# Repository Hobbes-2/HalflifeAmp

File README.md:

Halflife Amp

A portable amp made for the Hackclub Halflife! This amp is 100mm x 100mm total, including the case. It has three knobs, a female headphone jack, and a female aux jack. Its meant to be used with headphones or a aux speaker, as there is no built in speaker.

I was reading some books, as one does, and I was marveling at the various pieces of tech that people were carrying. Specifically, the "worse" of the such. Things like old battered phones, devices, the like. The cassette player from 20th Century Boys is what inspired me to do this particular project. (And the fact that I kept tripping on my headphones cord while playing my bass.) Its meant to have tape, stickers, and other such things on it - be imperfect. Its barely functional to be honest, but it works nonetheless, which personally i feel like adds to the character of the device. (Call me crazy) 

Schematics

PCB

3D Render

Case

:D

BOM

| Piece | Quantity | Price (USD) Total | Link |
|---|---:|---:|---|
| Capacitor 100nF | 3 | $0.33 | [DigiKey](https://www.digikey.com/en/products/detail/murata-electronics/GRM033R60J104KE19D/702433) |
| Capacitor 1µF | 2 | $0.20 | [DigiKey](https://www.digikey.com/en/products/detail/murata-electronics/GRM033R60G105MEA2D/2766944) |
| Capacitor 0.01µF | 1 | $0.11 | [DigiKey](https://www.digikey.com/en/products/detail/murata-electronics/GRM033R71A103KA01D/702460) |
| Capacitor 4.7µF | 3 | $2.19 | [DigiKey](https://www.digikey.com/en/products/detail/cal-chip-electronics-inc/GMC10X7R475K10NT/24343641) |
| Capacitor 470pF | 1 | $0.11 | [DigiKey](https://www.digikey.com/en/products/detail/murata-electronics/GRM033R71E471KA01D/702446) |
| Capacitor 10µF | 1 | $0.28 | [DigiKey](https://www.digikey.com/en/products/detail/cal-chip-electronics-inc/GMC21X6S106K6R3NT/28882501?s=N4IgjCBcoGwJxVAYygMwIYBsDOBTANCAPZQDaIALAAxwDMdIAuoQA4AuUIAymwE4CWAOwDmIAL6EATFQoJoIFJAw4CxMuCoACAK0AxJqw6QQAVUH82AeVQBZXOmwBXXrnGEAtAFZECtFjyEJJDkkkxi4UA) |
| Capacitor 100µF | 2 | $2.04 | [DigiKey](https://www.digikey.com/en/products/detail/cal-chip-electronics-inc/GMC31X6S107M4R0NT/30359890) |
| Audio Jack | 1 | $2.21 | [DigiKey](https://www.digikey.com/en/products/detail/switchcraft-inc/35RASMT4BHNTRX/1288817) |
| 9V Connector Pins | 1 | $0.41 | [DigiKey](https://www.digikey.com/en/products/detail/samtec-inc/SSA-102-W-T/1105910) |
| NJ2FD-V (Amp Jack) | 1 | $1.24 | [Mouser](https://www.mouser.com/en/ProductDetail/Neutrik/NJ2FD-V?qs=2AuUxvzm3x8JdKlzelpdqQ%3D%3D) |
| BC550 Transistor | 3 | $0.84 | [DigiKey](https://www.digikey.com/en/products/detail/onsemi/BC550CTA/974185?s=N4IgjCBcoLQKxVAYygMwIYBsDOBTANCAPZQDaIATCALoC%2BthVk5AQgMJxwAMABDYQDZEIAJYATKCBhguVQgAcALpJCFFAT3m5JY7CnpA) |
| Resistor 4.7kΩ | 4 | $0.40 | [DigiKey](https://www.digikey.com/en/products/detail/stackpole-electronics-inc/CF18JT4K70/1741708) |
| Resistor 100kΩ | 5 | $0.50 | [DigiKey](https://www.digikey.com/en/products/detail/stackpole-electronics-inc/CF18JT100K/1741564) |
| Resistor 10kΩ | 3 | $0.30 | [DigiKey](https://www.digikey.com/en/products/detail/stackpole-electronics-inc/CF18JT10K0/1741566) |
| Resistor 68kΩ | 1 | $0.10 | [DigiKey](https://www.digikey.com/en/products/detail/stackpole-electronics-inc/CFM14JT68K0/1742271) |
| Resistor 2.2kΩ | 1 | $0.10 | [DigiKey](https://www.digikey.com/en/products/detail/stackpole-electronics-inc/CF18JT2K20/1741619) |
| Resistor 3.3kΩ | 1 | $0.10 | [DigiKey](https://www.digikey.com/en/products/detail/stackpole-electronics-inc/CF18JT3K30/1741665) |
| Resistor 1.5kΩ | 1 | $0.10 | [DigiKey](https://www.digikey.com/en/products/detail/stackpole-electronics-inc/CFM14JT1K50/1742042) |
| Resistor 220kΩ | 1 | $0.10 | [DigiKey](https://www.digikey.com/en/products/detail/stackpole-electronics-inc/CF18JT220K/1741641) |
| TLV1117-33 | 1 | $0.46 | [DigiKey](https://www.digikey.com/en/products/detail/texas-instruments/TLV1117-33CDCYR/1216718) |
| TL072 | 1 | $1.00 | [DigiKey](https://www.digikey.com/en/products/detail/texas-instruments/TL072IP/563039) |
| Power (Dual 9V Battery Holder) | 1 | $7.00 | [Amazon](https://www.amazon.com/DaierTek-Battery-Holder-Switch-Black/dp/B07YBZ18VS/ref=sr_1_6?crid=1U9ZB5Y0CWZNM&dib=eyJ2IjoiMSJ9.WRwbqtY6HXsnho_s_Ua6KwJcvSdgK72wzs4y71n4mX0wuluCSoSpyxYBsTnNdWsVK5ykWO_P8_aoQiro7uqYw4BO5U566xs4aXB9pBMJ043hSb54WlC2Rm8CDNvTsYO0apJb04Nmt2BlHuVpW2ucP8qgKjfWmtev5D5PMKTWea-xYShZCzaWs1yMrRot46WSNp7Ux8LNu12TTWS7NfNXQYKgUgsd8yXQauVQrGsN2vo.Yd12tfIeqCmiwpr1zeERkcti0l5q6xaZQRHXPPpXT48&dib_tag=se&keywords=dual+9v+battery+holder&qid=1792977639&sprefix=dual+9v+battery+holder%2Caps%2C179&sr=8-6) |
| Potentiometer | 3 | $7.95 | [DigiKey](https://www.digikey.com/en/products/detail/tt-electronics-bi/P0915N-FC15BR100K/5957453?s=N4IgTCBcDaIAoAYCcBGArAOQLQDEDC6AQgEooIIDSIAugL5A) |
| PCB | 1 | $5.20 | [JLCPCB](https://jlcpcb.com/) |
| Case | 1 | — | Printing Legion |

## Cost Summary

| Item | Amount (USD) |
|---|---:|
| Tax | $28.70 |
| **Total** | **$61.97** |

*Anything over the 65 for printing legion will be payed out of pocket, thank you!

(BOM formatted for .MD by AI)

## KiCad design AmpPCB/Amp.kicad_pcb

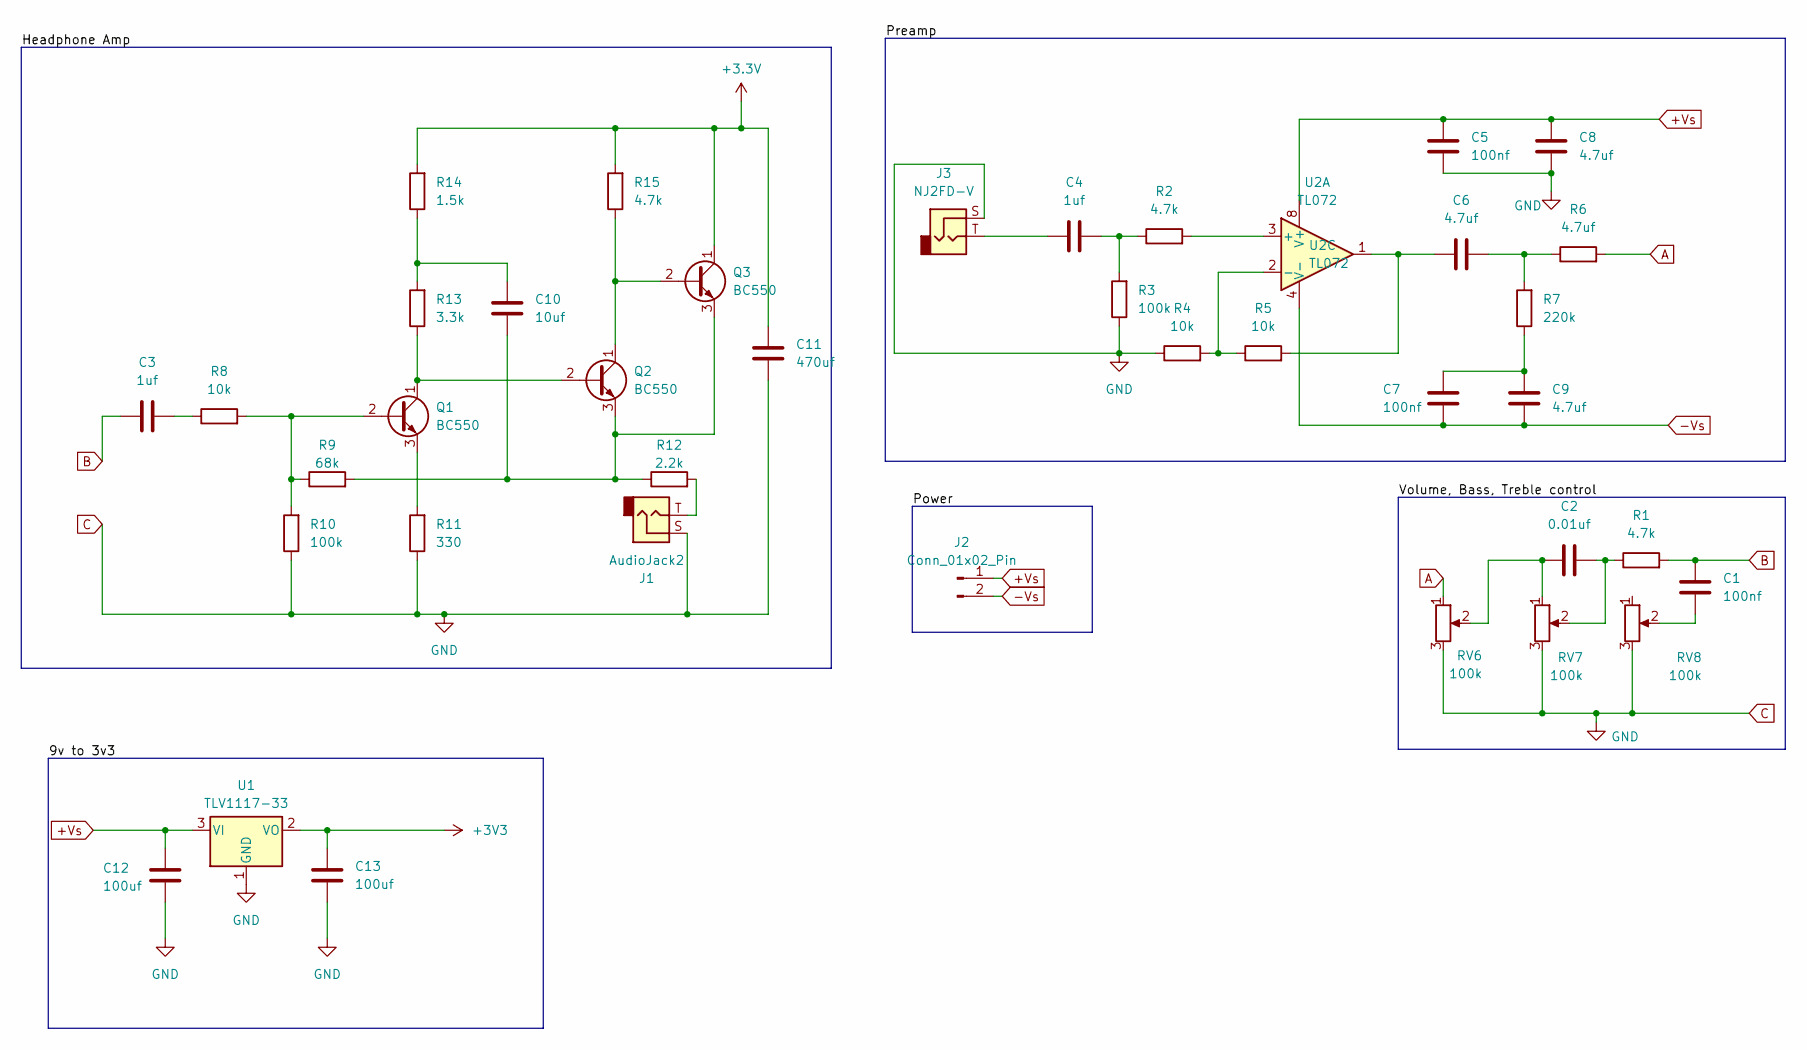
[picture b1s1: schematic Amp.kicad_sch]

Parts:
C1, C5, C7: 100nf; C_1206_3216Metric
C2: 0.01uf; C_1206_3216Metric
C3, C4: 1uf; C_1206_3216Metric
C6, C8, C9: 4.7uf; C_1206_3216Metric
C10: 10uf; C_1206_3216Metric
C11: 470uf; C_1206_3216Metric
C12, C13: 100uf; C_1206_3216Metric
J1: AudioJack2; Jack_3.5mm_Switronic_ST-005-G_horizontal
J2: Conn_01x02_Pin; PinSocket_1x02_P2.54mm_Vertical_SMD_Pin1Left
J3: NJ2FD-V; Jack_6.35mm_Neutrik_NJ2FD-V_Vertical
Q1, Q2, Q3: BC550; TO-92_Inline
R1, R2, R15: 4.7k; R_Axial_DIN0204_L3.6mm_D1.6mm_P7.62mm_Horizontal
R3, R10: 100k; R_Axial_DIN0204_L3.6mm_D1.6mm_P7.62mm_Horizontal
R4, R5, R8: 10k; R_Axial_DIN0204_L3.6mm_D1.6mm_P7.62mm_Horizontal
R6: 4.7uf; R_Axial_DIN0204_L3.6mm_D1.6mm_P7.62mm_Horizontal
R7: 220k; R_Axial_DIN0204_L3.6mm_D1.6mm_P7.62mm_Horizontal
R9: 68k; R_Axial_DIN0204_L3.6mm_D1.6mm_P7.62mm_Horizontal
R11: 330; R_Axial_DIN0204_L3.6mm_D1.6mm_P7.62mm_Horizontal
R12: 2.2k; R_Axial_DIN0204_L3.6mm_D1.6mm_P7.62mm_Horizontal
R13: 3.3k; R_Axial_DIN0204_L3.6mm_D1.6mm_P7.62mm_Horizontal
R14: 1.5k; R_Axial_DIN0204_L3.6mm_D1.6mm_P7.62mm_Horizontal
RV6, RV7, RV8: 100k; Potentiometer_TT_P0915N
U1: TLV1117-33; SOT-223-3_TabPin2
U2: TL072; DIP-8_W7.62mm

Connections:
+3.3V: C11.1, Q3.1 (C), R14.2, R15.2
+3V3: C13.2, U1.2 (VO)
+Vs: C5.2, C8.2, C12.2, J2.1, U1.3 (VI), U2.8 (V+)
-Vs: C7.1, C9.1, J2.2, U2.4 (V-)
A: R6.2, RV6.1
B: C1.1, C3.2, R1.2
C: C5.1, C8.1, C11.2, C12.1, C13.1, J1.S, J3.S, R3.1, R4.1, R10.1, R11.1, RV6.3, RV7.3, RV8.3, U1.1 (GND)
unnamed: C1.2, RV8.2
unnamed: C2.1, RV6.2, RV7.1
unnamed: C2.2, R1.1, RV7.2
unnamed: C3.1, R8.1
unnamed: C4.1, J3.T
unnamed: C4.2, R2.1, R3.2
unnamed: C6.1, R6.1, R7.2
unnamed: C6.2, R5.2, U2.1
unnamed: C7.2, C9.2, R7.1
unnamed: C10.1, R13.2, R14.1
unnamed: J1.T, R12.2
unnamed: Q1.2 (B), R8.2, R9.1, R10.2
unnamed: Q1.1 (C), Q2.2 (B), R13.1
unnamed: Q1.3 (E), R11.2
unnamed: Q2.1 (C), Q3.2 (B), R15.1
unnamed: C10.2, Q2.3 (E), Q3.3 (E), R9.2, R12.1
unnamed: R2.2, U2.3 (+)
unnamed: R4.2, R5.1, U2.2 (-)

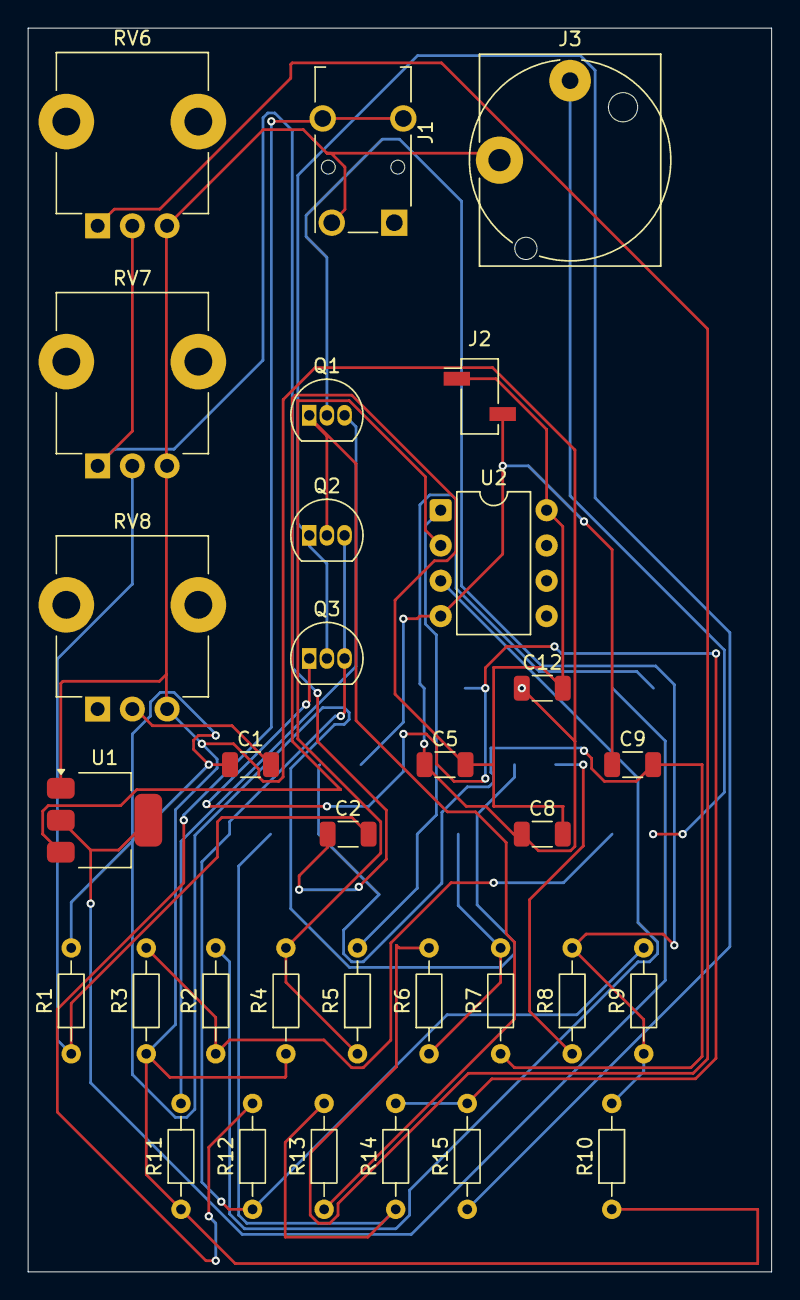
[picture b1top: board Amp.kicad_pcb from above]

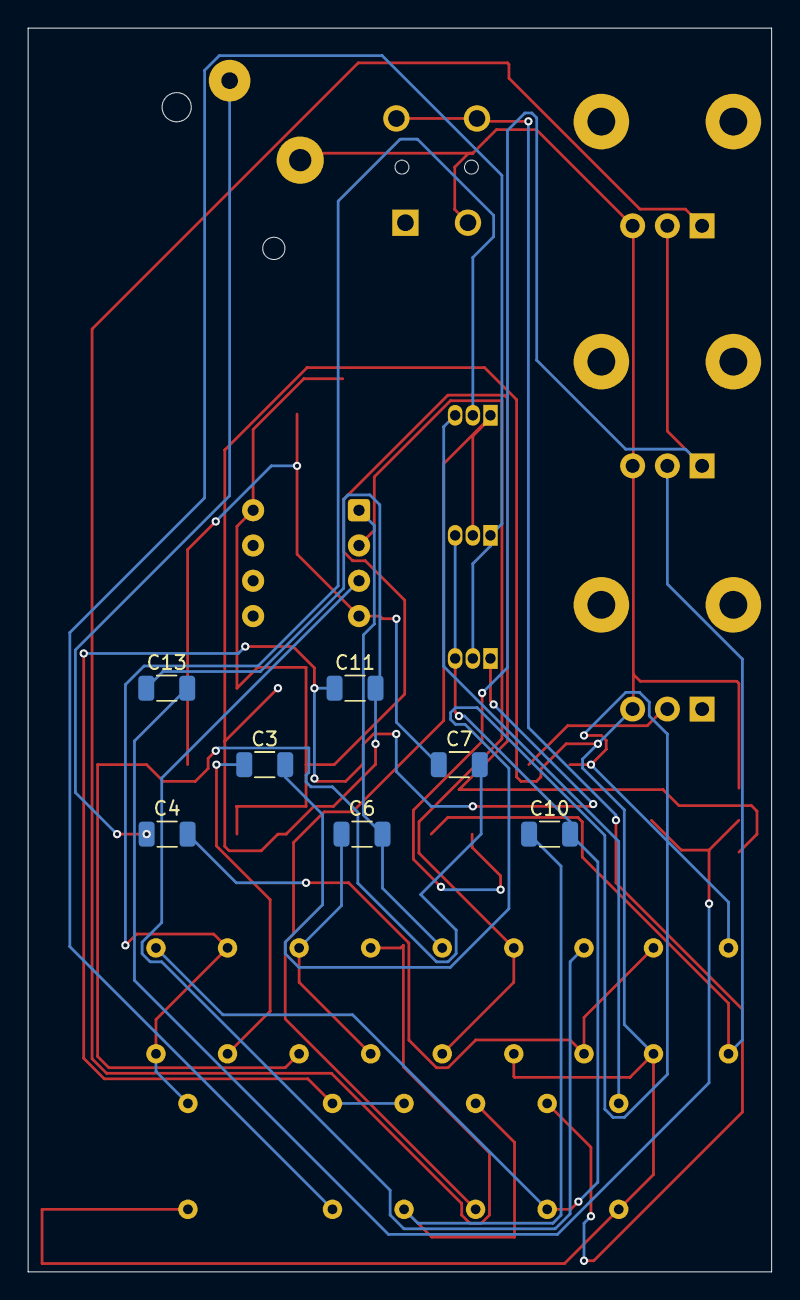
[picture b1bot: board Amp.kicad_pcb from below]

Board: 2 copper layers, 53.5 x 89.5 mm, 39 parts (7 on the bottom side), 25 nets.

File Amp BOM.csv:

Part,Number,Price (USD),Link
Capacitor 100nf,3,0.33,https://www.digikey.com/en/products/detail/murata-electronic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
Capacitor 1uf,2,0.2,https://www.digikey.com/en/products/detail/murata-electronic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
Capacitor 0.01uf,1,0.11,https://www.digikey.com/en/products/detail/murata-electronic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
Capacitor 4.7uf,3,2.19,https://www.digikey.com/en/products/detail/cal-chip-electron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
Capacitor 470pf,1,0.11,https://www.digikey.com/en/products/detail/murata-electronic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
Capacitor 10uf,1,0.28,https://www.digikey.com/en/products/detail/cal-chip-electron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
Capacitor 100uf,2,2.04,https://www.digikey.com/en/products/detail/cal-chip-electron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
Audio Jack,1,2.21,https://www.digikey.com/en/products/detail/switchcraft-inc/3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
9v Connector Pins,1,0.41,https://www.digikey.com/en/products/detail/samtec-inc/SSA-10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
NJ2FD-V (Amp jack),1,1.24,https://www.mouser.com/en/ProductDetail/Neutrik/NJ2FD-V?qs=2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
BC550 Transistor,3,0.84,https://www.digikey.com/en/products/detail/onsemi/BC550CTA/9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
Resistor 4.7k,4,0.4,https://www.digikey.com/en/products/detail/stackpole-electro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
Resistor 100k,5,0.5,https://www.digikey.com/en/products/detail/stackpole-electro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
Resistor 10k,3,0.3,https://www.digikey.com/en/products/detail/stackpole-electro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
Resistor 68k,1,0.1,https://www.digikey.com/en/products/detail/stackpole-electro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
Resistor 2.2k,1,0.1,https://www.digikey.com/en/products/detail/stackpole-electro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
Resistor 3.3k,1,0.1,https://www.digikey.com/en/products/detail/stackpole-electro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
Resistor 1.5k,1,0.1,https://www.digikey.com/en/products/detail/stackpole-electro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
Resistor 220k,1,0.1,https://www.digikey.com/en/products/detail/stackpole-electro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
TLV1117-33,1,0.46,https://www.digikey.com/en/products/detail/texas-instruments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
TL072,1,1,https://www.digikey.com/en/products/detail/texas-instruments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
Power,1,7,https://www.amazon.com/DaierTek-Battery-Holder-Switch-Black/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
Potentiometer ,3,7.95,https://www.digikey.com/en/products/detail/tt-electronics-bi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
PCB,1,5.2,https://jlcpcb.com/
Case,1,,Printing legion
,,,
Total tax,,28.7,
Total,,61.97,
